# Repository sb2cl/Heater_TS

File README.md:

# Control de temperatura de un mini-biorreactor mediante un sensor de infrarrojos

Este repositorio recopila el código generado por Roberto Mateu en el desarrollo de su TFG.

## Matlab

La carpeta "1_IdentificacionModelo" contiene el código necesario para obtener modelos a partir de los datos experimentales de un bucle abierto mediante la herramienta SystemIdent. Además se incluye un ejemplo: datos reales e imágenes del modelo obtenido.

La carpeta "2_ValidacionModelo" contiene el código necesario para implementar el modelo obtenido en un simulador y comprobar si coincide con los datos experimentales.

Por último, la carpeta "3_SimuladorSimulink", contiene un simulador de un bucle de control en lazo cerrado con control de referencia.

## PCB

En la carpeta "pcb" se incluyen todos los archivos de Eagle usados para desarrollar/implementar la pcb del calentador basado en resistencias planas. También se incluyen imágenes con los resultados.

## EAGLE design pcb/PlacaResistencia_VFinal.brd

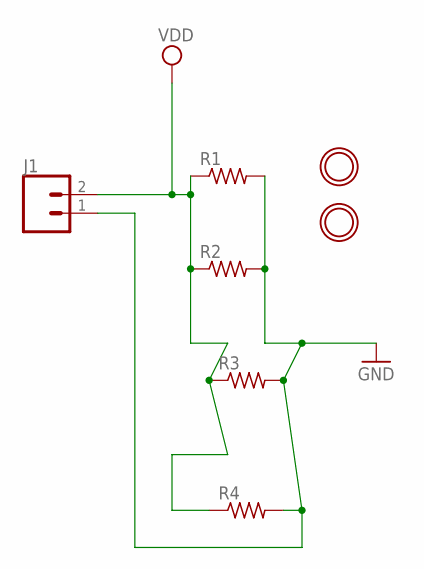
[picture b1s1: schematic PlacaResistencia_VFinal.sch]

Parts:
GND, GND2: MOUNTINGHOLE2.5; MOUNTINGHOLE_2.5_PLATED
J1: CONN_02; 1X02
R1, R2, R3, R4: R-US_R2512; R2512

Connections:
GND: J1.1, R1.2, R2.2, R3.2, R4.2
VDD: J1.2, R1.1, R2.1, R3.1, R4.1

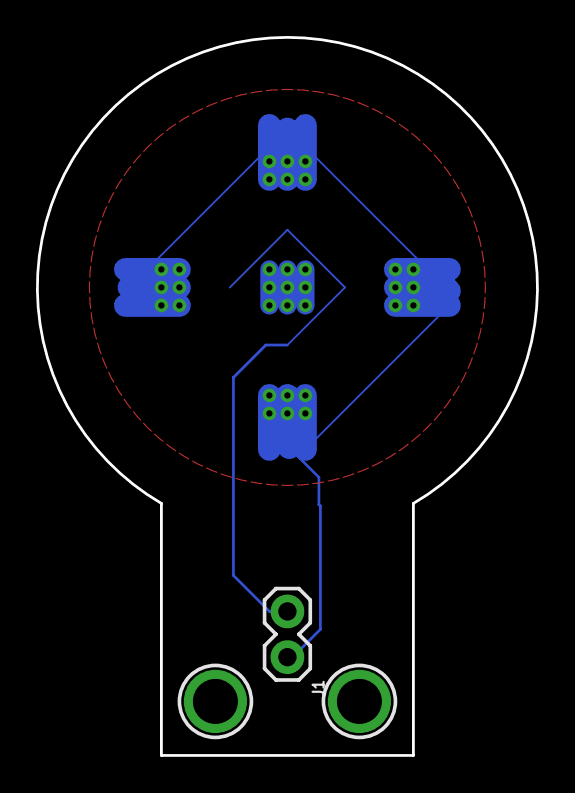
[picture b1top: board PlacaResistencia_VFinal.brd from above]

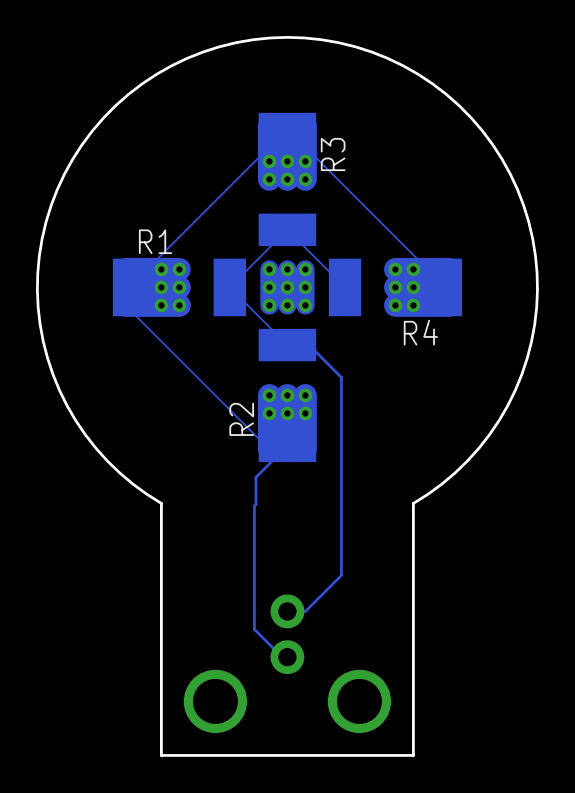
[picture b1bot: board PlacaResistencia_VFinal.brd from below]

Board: 2 copper layers, 27.8 x 39.9 mm, 7 parts (4 on the bottom side), 2 nets.

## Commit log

2021-06-29 Inital commmit
2021-06-29 Typo
2021-06-29 add matlab and pcb
2021-06-29 Add controlador embebido

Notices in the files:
parts and their libraries:
SparkFun-Connectors: Licensing: Creative Commons ShareAlike 4.0 International - https://creativecommons.org/licenses/by-sa/4.0
microbuilder: This work is placed in the public domain, and may be freely used for commercial and non-commercial work with the following conditions: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
